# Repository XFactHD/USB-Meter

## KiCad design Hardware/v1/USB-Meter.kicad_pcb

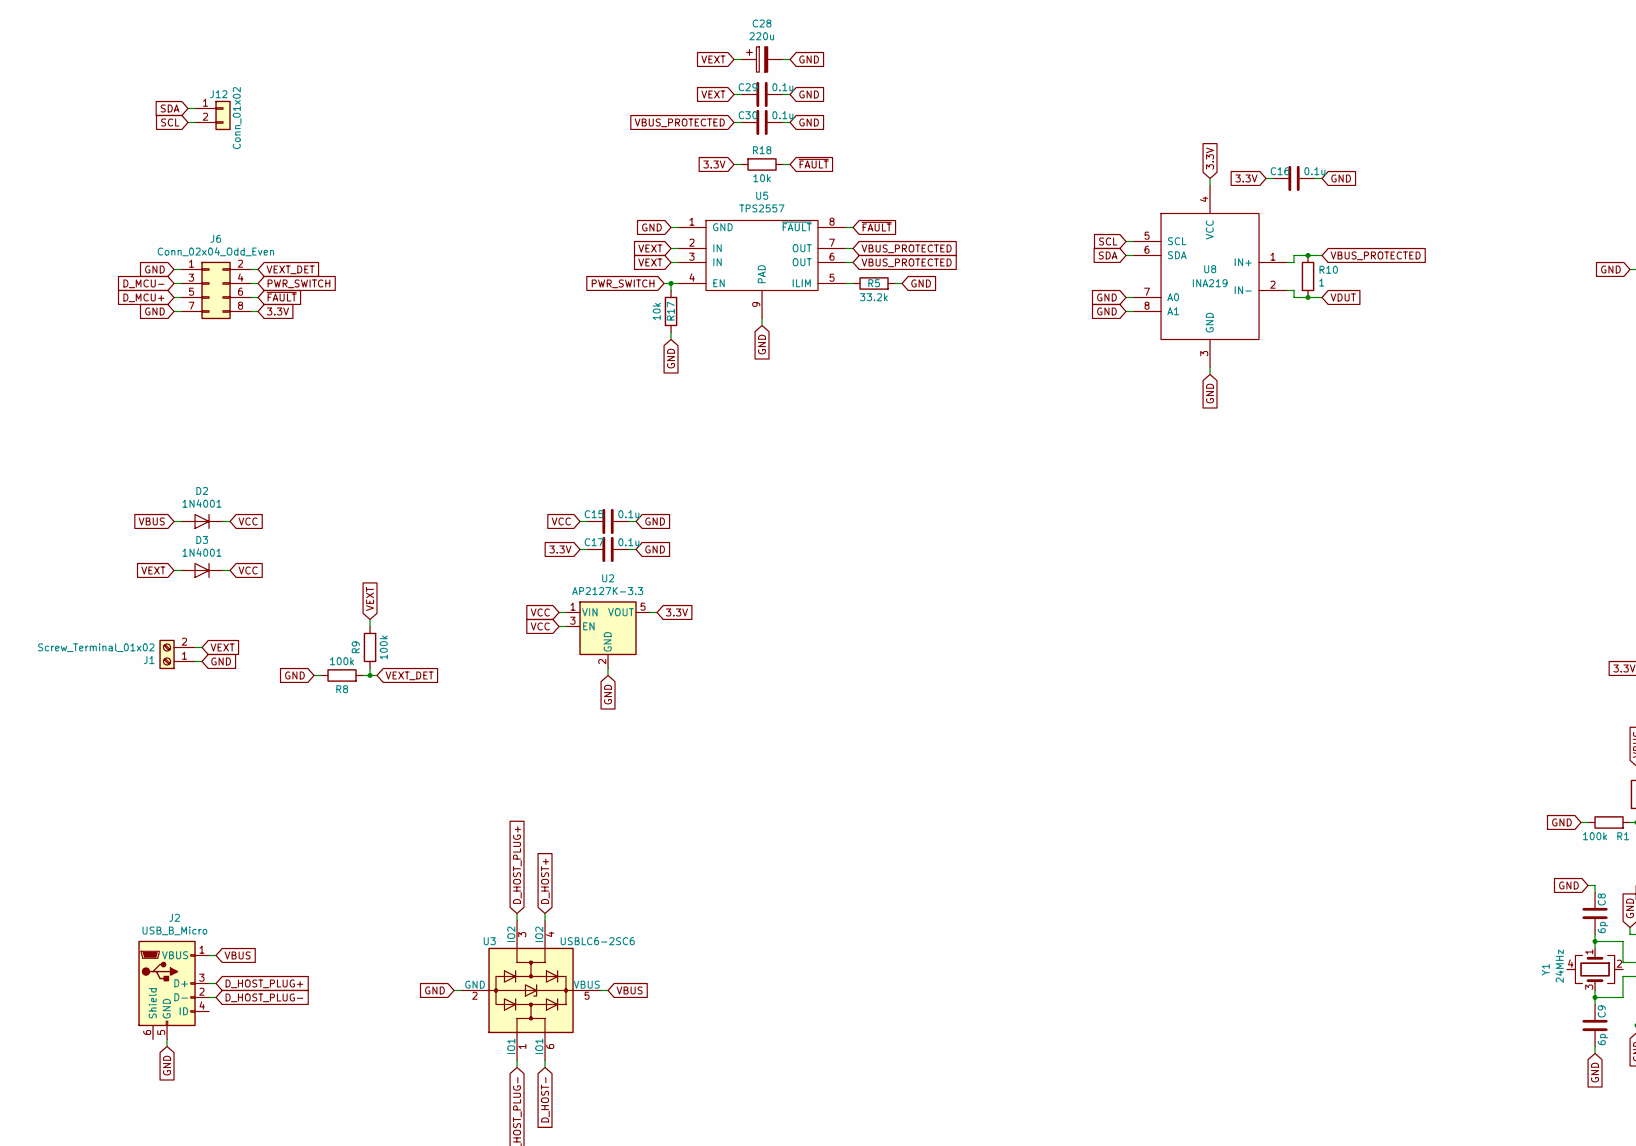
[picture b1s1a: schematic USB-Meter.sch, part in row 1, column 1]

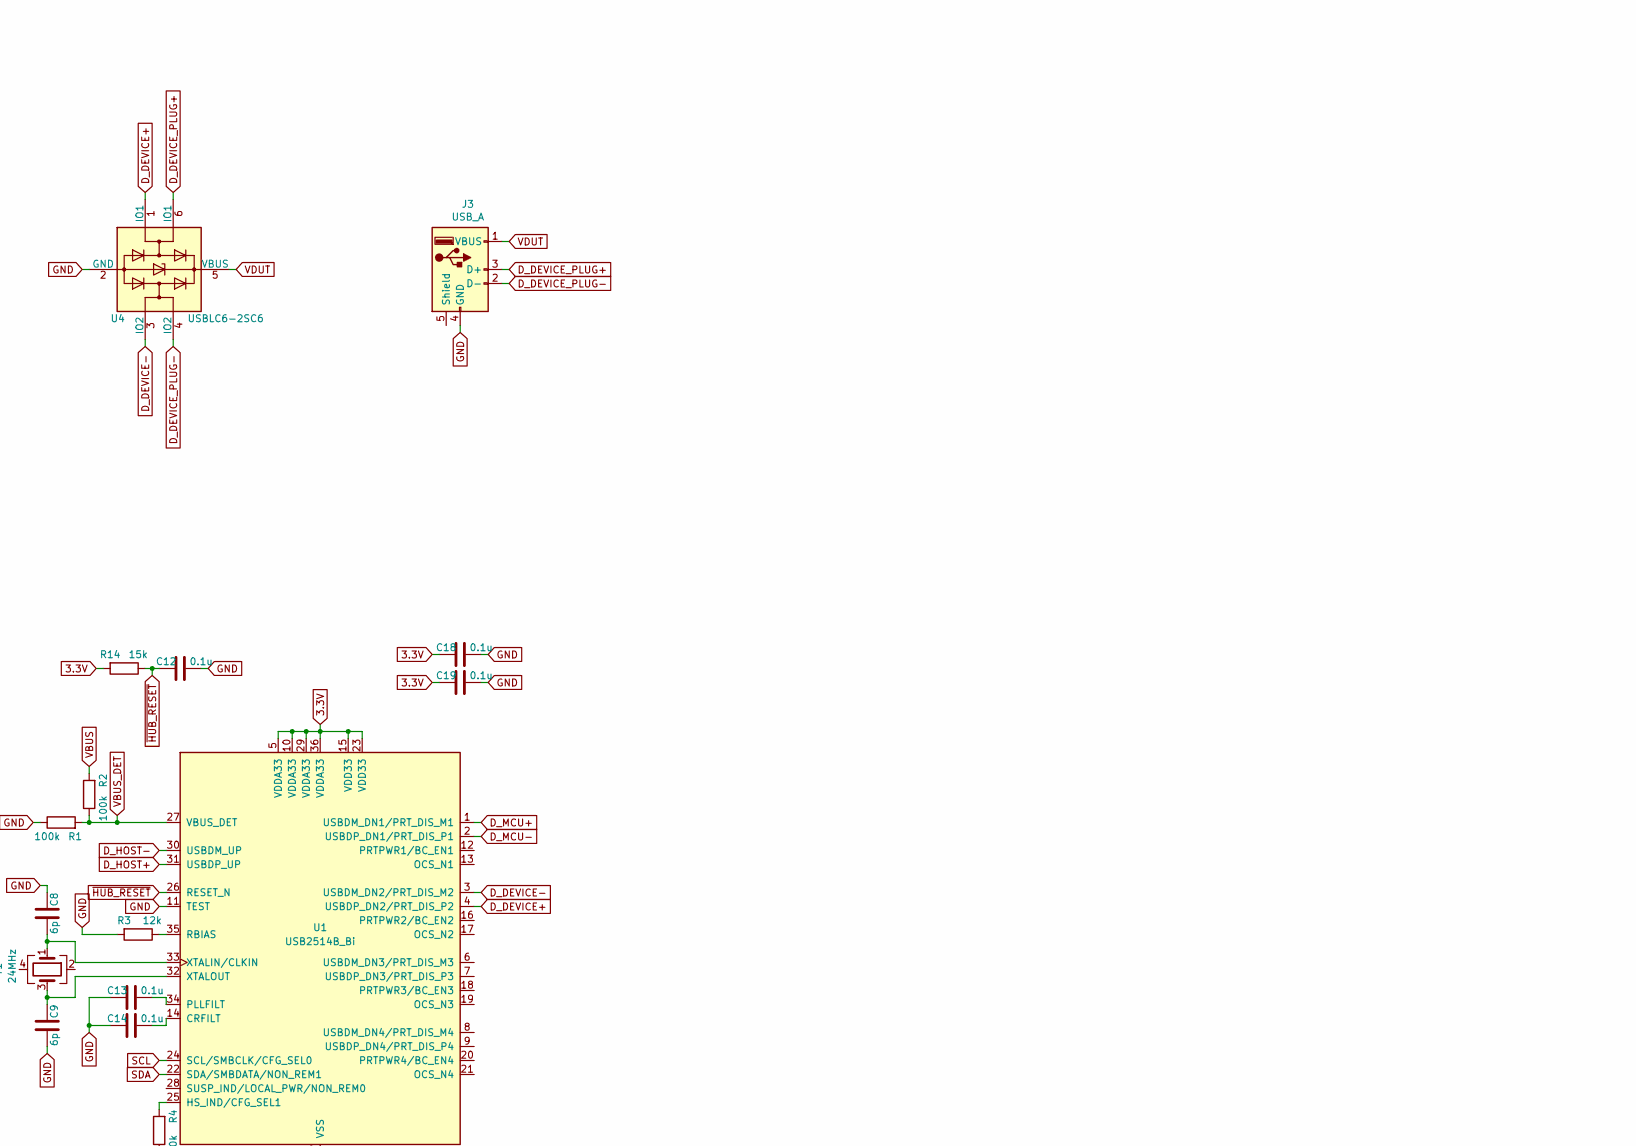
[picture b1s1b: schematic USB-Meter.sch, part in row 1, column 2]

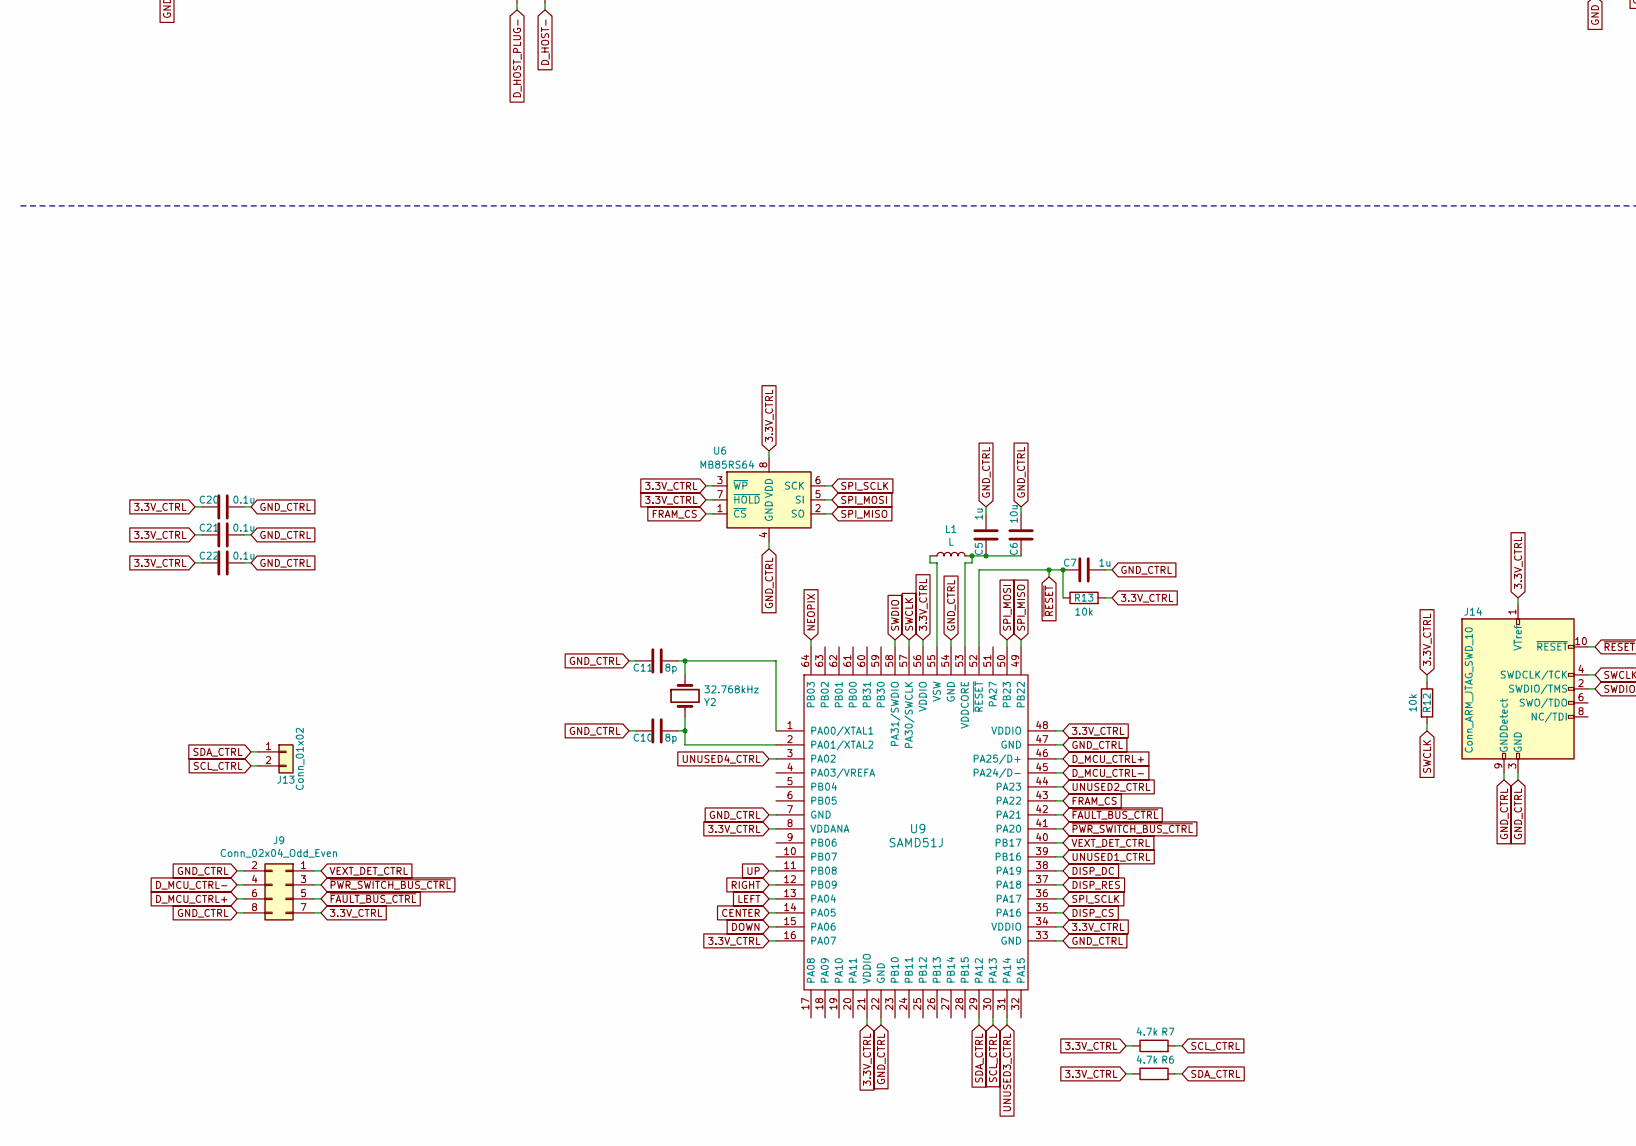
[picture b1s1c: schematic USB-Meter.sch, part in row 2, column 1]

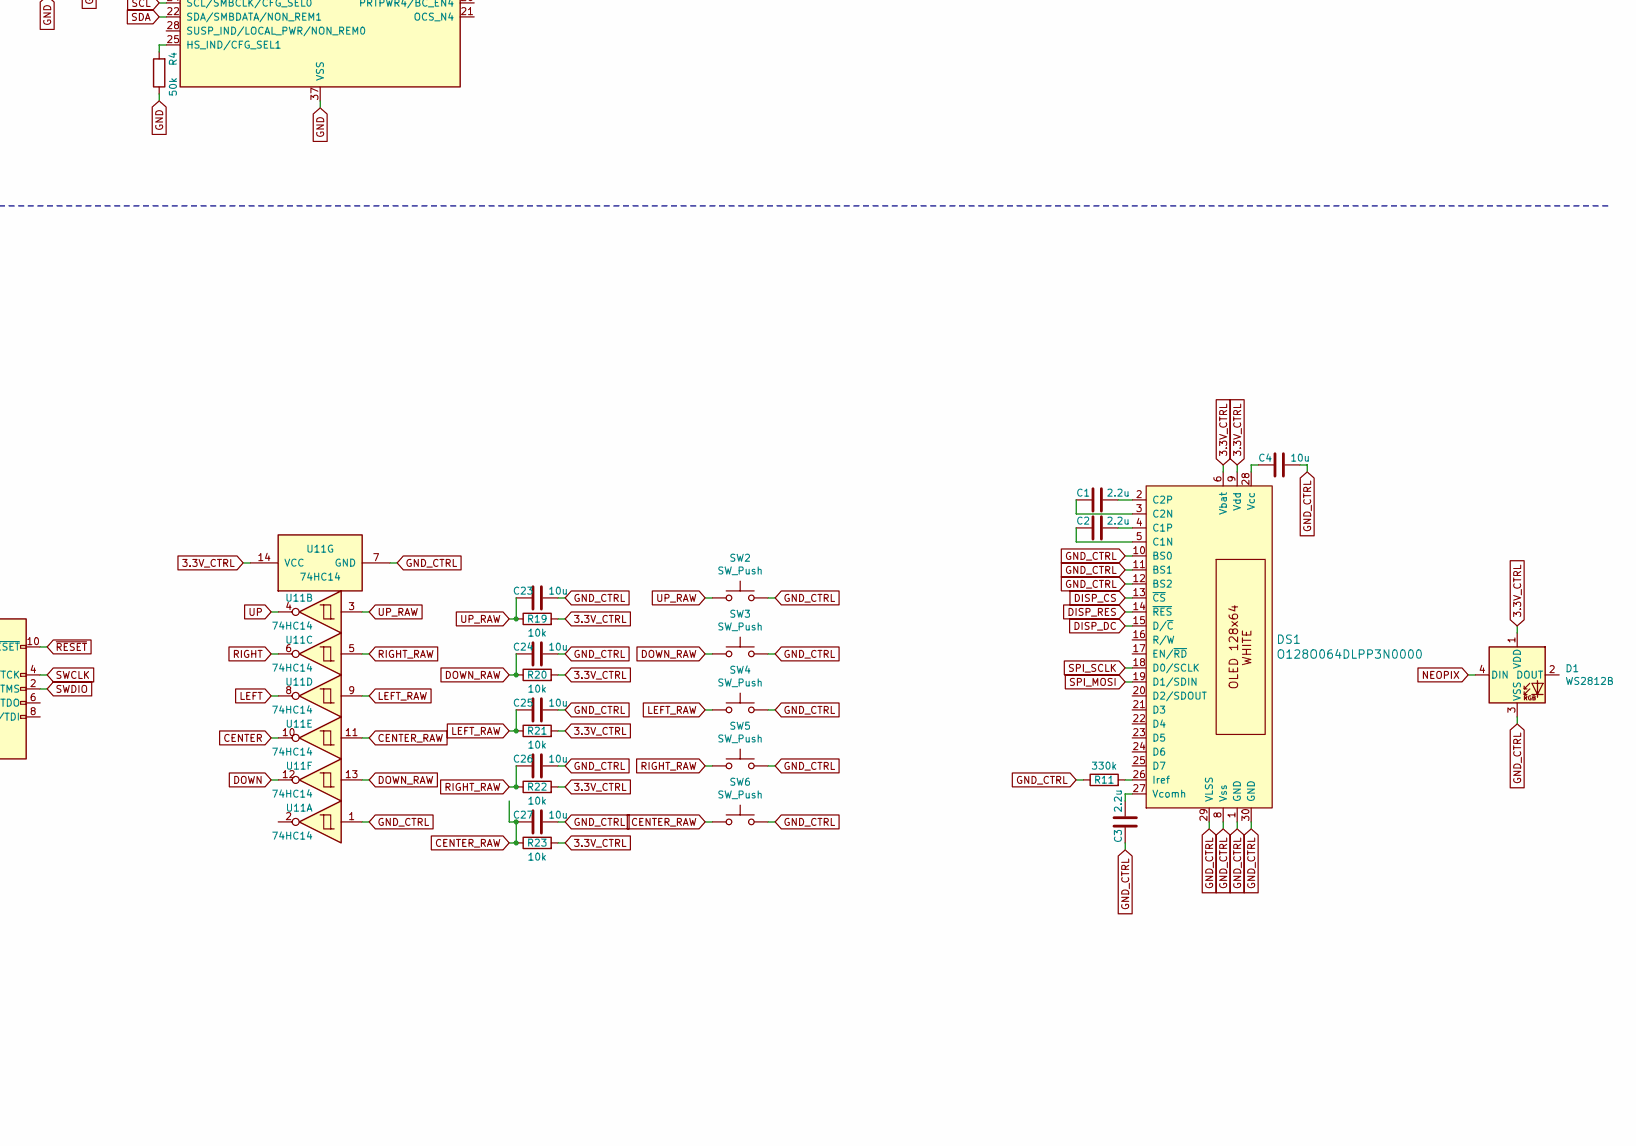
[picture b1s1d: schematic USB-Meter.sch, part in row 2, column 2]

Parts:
C1, C2, C3: 2.2u; C_0805
C4, C6, C23, C24, C25, C26, C27: 10u; C_0805
C5, C7: 1u; C_0805
C8, C9: 6p; C_0805
C10, C11: 8p; C_0805
C12, C13, C14, C15, C16, C17, C18, C19, C20, C21, C22, C29, C30: 0.1u; C_0805
C28: 220u; CP_Tantalum_Case-D_EIA-7343-31_Reflow
D1: WS2812B; LED_WS2812B-PLCC4
D2, D3: 1N4001; D_SOD-123
DS1: O128O064DLPP3N0000; OLED_O128O064D-LPP3N00000
J1: Screw_Terminal_01x02; PhoenixContact_PTSM0,5_2-2,5-V
J2: USB_B_Micro; USB_Micro-B_Molex_47346-0001
J3: USB_A
J6: Conn_02x04_Odd_Even; Pin_Header_Straight_2x04_Pitch1.27mm
J9: Conn_02x04_Odd_Even; Pin_Header_Straight_2x04_Pitch1.27mm_SMD
J12, J13: Conn_01x02; Pin_Header_Straight_1x02_Pitch1.27mm
J14: Conn_ARM_JTAG_SWD_10; Pin_Header_Straight_2x05_Pitch1.27mm
L1: L; L_0805
R1, R2, R8, R9: 100k; R_0805
R3: 12k; R_0805
R4: 50k; R_0805
R5: 33.2k; R_0805
R6, R7: 4.7k; R_0805
R10: 1; R_2512
R11: 330k; R_0805
R12, R13, R17, R18, R19, R20, R21, R22, R23: 10k; R_0805
R14: 15k; R_0805
SW2, SW3, SW4, SW5, SW6: SW_Push; SW_PUSH_6mm
U1: USB2514B_Bi; QFN-36-1EP_6x6mm_Pitch0.5mm
U2: AP2127K-3.3; SOT-23-5
U3, U4: USBLC6-2SC6; SOT-23-6
U5: TPS2557; DFN-8-1EP_3x3mm_Pitch0.65mm
U6: MB85RS64; SOIC-8_3.9x4.9mm_Pitch1.27mm
U8: INA219; SOT-23-8
U9: SAMD51J; TQFP-64_10x10mm_Pitch0.5mm
U11: 74HC14
Y1: 24MHz; Crystal_SMD_2016-4pin_2.0x1.6mm
Y2: 32.768kHz; Crystal_SMD_3215-2pin_3.2x1.5mm

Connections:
3.3V: C16.2, C17.2, C18.2, C19.2, J6.8, R14.2, R18.2, U1.5 (VDDA33), U1.10 (VDDA33), U1.15 (VDD33), U1.23 (VDD33), U1.29 (VDDA33), U1.36 (VDDA33), U2.5 (VOUT), U8.4 (VCC)
3.3V_CTRL: C20.2, C21.2, C22.2, D1.1 (VDD), DS1.6 (Vbat), DS1.9 (Vdd), J9.7, J14.1 (VTref), R6.1, R7.1, R12.1, R13.2, R19.2, R20.2, R21.2, R22.2, R23.2, U6.3 (~WP), U6.7 (~HOLD), U6.8 (VDD), U9.8 (VDDANA), U9.16 (PA07), U9.21 (VDDIO), U9.34 (VDDIO), U9.48 (VDDIO), U9.56 (VDDIO), U11.14 (VCC)
CENTER: U9.14 (PA05), U11.10
CENTER_RAW: C27.2, R23.1, SW6.1, U11.11
DISP_CS: DS1.13 (~CS), U9.35 (PA16)
DISP_DC: DS1.15 (D/~C), U9.38 (PA19)
DISP_RES: DS1.14 (~RES), U9.37 (PA18)
DOWN: U9.15 (PA06), U11.12
DOWN_RAW: C24.2, R20.1, SW3.1, U11.13
D_DEVICE+: U1.4 (USBDP_DN2/PRT_DIS_P2), U4.1 (IO1)
D_DEVICE-: U1.3 (USBDM_DN2/PRT_DIS_M2), U4.3 (IO2)
D_DEVICE_PLUG+: J3.3 (D+), U4.6 (IO1)
D_DEVICE_PLUG-: J3.2 (D-), U4.4 (IO2)
D_HOST+: U1.31 (USBDP_UP), U3.4 (IO2)
D_HOST-: U1.30 (USBDM_UP), U3.6 (IO1)
D_HOST_PLUG+: J2.3 (D+), U3.3 (IO2)
D_HOST_PLUG-: J2.2 (D-), U3.1 (IO1)
D_MCU+: J6.5, U1.1 (USBDM_DN1/PRT_DIS_M1)
D_MCU-: J6.3, U1.2 (USBDP_DN1/PRT_DIS_P1)
D_MCU_CTRL+: J9.6, U9.46 (PA25/D+)
D_MCU_CTRL-: J9.4, U9.45 (PA24/D-)
FRAM_CS: U6.1 (~CS), U9.43 (PA22)
GND: C8.2, C9.1, C12.1, C13.2, C14.2, C15.1, C16.1, C17.1, C18.1, C19.1, C28.2, C29.1, C30.1, J1.1, J2.5 (GND), J3.4 (GND), J6.1, J6.7, R1.1, R3.2, R4.1, R5.2, R8.1, R17.2, U1.11 (TEST), U1.37 (VSS), U2.2 (GND), U3.2 (GND), U4.2 (GND), U5.1 (GND), U5.9 (PAD), U8.3 (GND), U8.7 (A0), U8.8 (A1)
GND_CTRL: C3.2, C4.1, C5.1, C6.1, C7.1, C10.2, C11.2, C20.1, C21.1, C22.1, C23.1, C24.1, C25.1, C26.1, C27.1, D1.3 (VSS), DS1.1 (GND), DS1.8 (Vss), DS1.10 (BS0), DS1.11 (BS1), DS1.12 (BS2), DS1.29 (VLSS), DS1.30 (GND), J9.2, J9.8, J14.3 (GND), J14.5 (GND), J14.9 (GNDDetect), R11.1, SW2.2, SW3.2, SW4.2, SW5.2, SW6.2, U6.4 (GND), U9.7 (GND), U9.22 (GND), U9.33 (GND), U9.47 (GND), U9.54 (GND), U11.1, U11.7 (GND)
LEFT: U9.13 (PA04), U11.8
LEFT_RAW: C25.2, R21.1, SW4.1, U11.9
NEOPIX: D1.4 (DIN), U9.64 (PB03)
unnamed: C1.1, DS1.2 (C2P)
unnamed: C1.2, DS1.3 (C2N)
unnamed: C2.1, DS1.4 (C1P)
unnamed: C2.2, DS1.5 (C1N)
unnamed: C3.1, DS1.27 (Vcomh)
unnamed: C4.2, DS1.28 (Vcc)
unnamed: C5.2, C6.2, L1.2, U9.53 (VDDCORE)
unnamed: C8.1, U1.33 (XTALIN/CLKIN), Y1.1
unnamed: C9.2, U1.32 (XTALOUT), Y1.3
unnamed: C10.1, U9.2 (PA01/XTAL2), Y2.2
unnamed: C11.1, U9.1 (PA00/XTAL1), Y2.1
unnamed: C13.1, U1.34 (PLLFILT)
unnamed: C14.1, U1.14 (CRFILT)
unnamed: DS1.26 (Iref), R11.2
unnamed: L1.1, U9.55 (VSW)
unnamed: R3.1, U1.35 (RBIAS)
unnamed: R4.2, U1.25 (HS_IND/CFG_SEL1)
unnamed: R5.1, U5.5 (ILIM)
PWR_SWITCH: J6.4, R17.1, U5.4 (EN)
RIGHT: U9.12 (PB09), U11.6
RIGHT_RAW: C26.2, R22.1, SW5.1, U11.5
SCL: J12.2, U1.24 (SCL/SMBCLK/CFG_SEL0), U8.5 (SCL)
SCL_CTRL: J13.2, R7.2, U9.30 (PA13)
SDA: J12.1, U1.22 (SDA/SMBDATA/NON_REM1), U8.6 (SDA)
SDA_CTRL: J13.1, R6.2, U9.29 (PA12)
SPI_MISO: U6.2 (SO), U9.49 (PB22)
SPI_MOSI: DS1.19 (D1/SDIN), U6.5 (SI), U9.50 (PB23)
SPI_SCLK: DS1.18 (D0/SCLK), U6.6 (SCK), U9.36 (PA17)
SWCLK: J14.4 (SWDCLK/TCK), R12.2, U9.57 (PA30/SWCLK)
SWDIO: J14.2 (SWDIO/TMS), U9.58 (PA31/SWDIO)
UNUSED1_CTRL: U9.39 (PB16)
UNUSED2_CTRL: U9.44 (PA23)
UNUSED3_CTRL: U9.31 (PA14)
UNUSED4_CTRL: U9.3 (PA02)
UP: U9.11 (PB08), U11.4
UP_RAW: C23.2, R19.1, SW2.1, U11.3
VBUS: D2.2 (A), J2.1 (VBUS), R2.2, U3.5 (VBUS)
VBUS_DET: R1.2, R2.1, U1.27 (VBUS_DET)
VBUS_PROTECTED: C30.2, R10.1, U5.6 (OUT), U5.7 (OUT), U8.1 (IN+)
VCC: C15.2, D2.1 (K), D3.1 (K), U2.1 (VIN), U2.3 (EN)
VDUT: J3.1 (VBUS), R10.2, U4.5 (VBUS), U8.2 (IN-)
VEXT: C28.1, C29.2, D3.2 (A), J1.2, R9.2, U5.2 (IN), U5.3 (IN)
VEXT_DET: J6.2, R8.2, R9.1
VEXT_DET_CTRL: J9.1, U9.40 (PB17)
~FAULT: J6.6, R18.1, U5.8 (~FAULT)
~FAULT_BUS_CTRL: J9.5, U9.42 (PA21)
~HUB_RESET: C12.2, R14.1, U1.26 (RESET_N)
~PWR_SWITCH_BUS_CTRL: J9.3, U9.41 (PA20)
~RESET: C7.2, J14.10 (~RESET~), R13.1, U9.52 (~RESET)

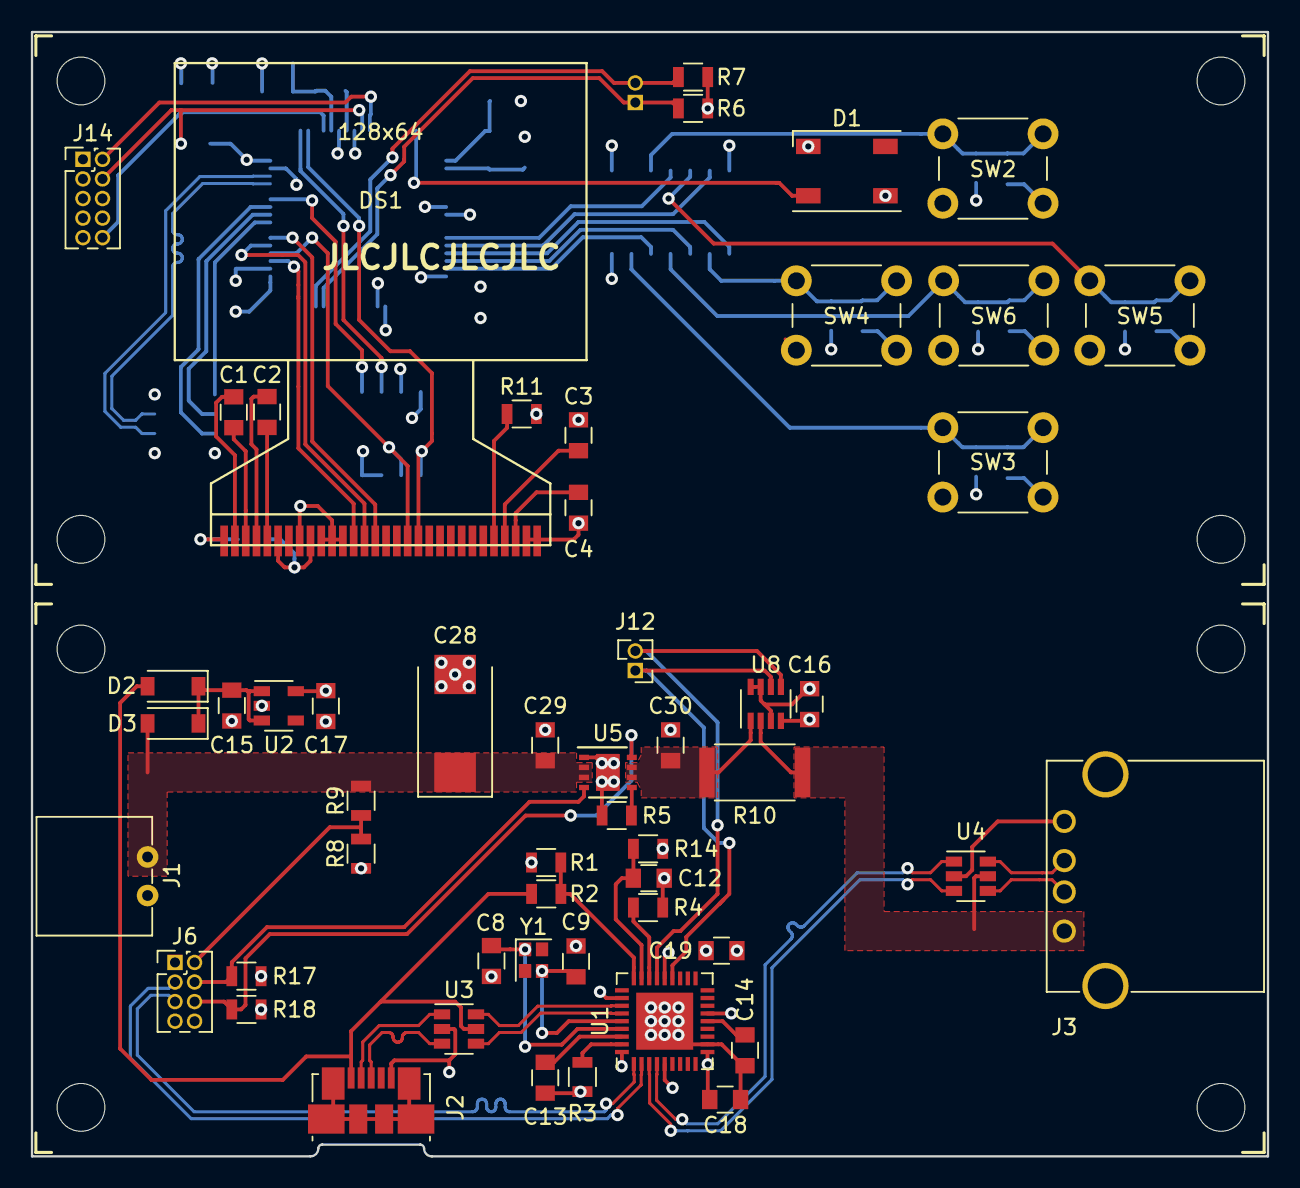
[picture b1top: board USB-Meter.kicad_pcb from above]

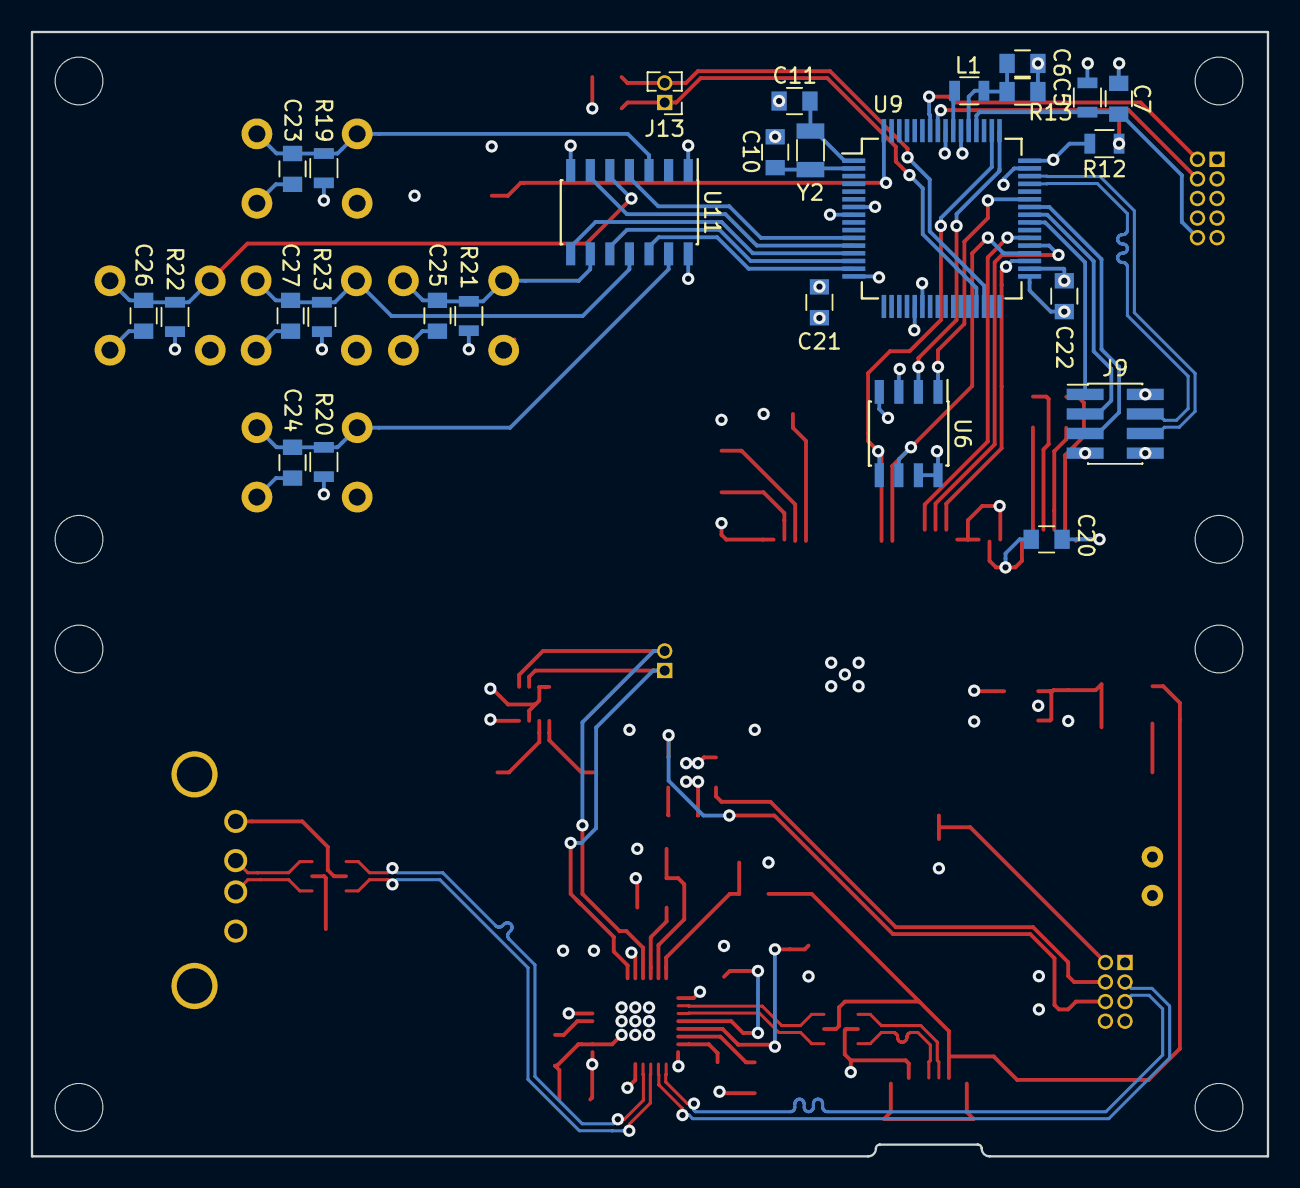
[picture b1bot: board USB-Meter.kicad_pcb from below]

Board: 4 copper layers, 80.1 x 72.9 mm, 80 parts (27 on the bottom side), 72 nets.

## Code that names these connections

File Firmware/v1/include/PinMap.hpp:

#ifndef PIN_MAP_H
#define PIN_MAP_H

#define SWITCH_FAULT 11    //Low => power switch detected a fault (oc or temp) and throttled power output
#define POWER_SWITCH 10    //Low => power off, High => power on
#define EXT_POWER_DETECT 0 //High => external power is applied

#define DISP_DC 9
#define DISP_RESET 6
#define DISP_CS 5

#define FRAM_CS 12

#define BUTTON_UP A2
#define BUTTON_DOWN A5
#define BUTTON_LEFT A4
#define BUTTON_RIGHT A3
#define BUTTON_CENTER A1

#endif

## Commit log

2020-12-18 Add Software V1
2020-12-18 Add Hardware V1
2020-12-18 Add Firmware V1
2020-12-18 Fix schematic library refs
2020-12-18 Create LICENSE
2021-04-03 Update USB-PowerLogger v1 to Java 11
2021-04-05 Remove options menu, move its contents to the main menu
2021-04-05 Start writing USB-PowerLogger v2 in Qt5
2021-04-29 Licensing
